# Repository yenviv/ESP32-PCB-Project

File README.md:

# ESP32-PCB-Project

https://docs.google.com/document/d/1k7oXqKPPIyiNBScuKdaxDys5A82Lqltt7Ke-TY6Z6dU/edit?usp=sharing

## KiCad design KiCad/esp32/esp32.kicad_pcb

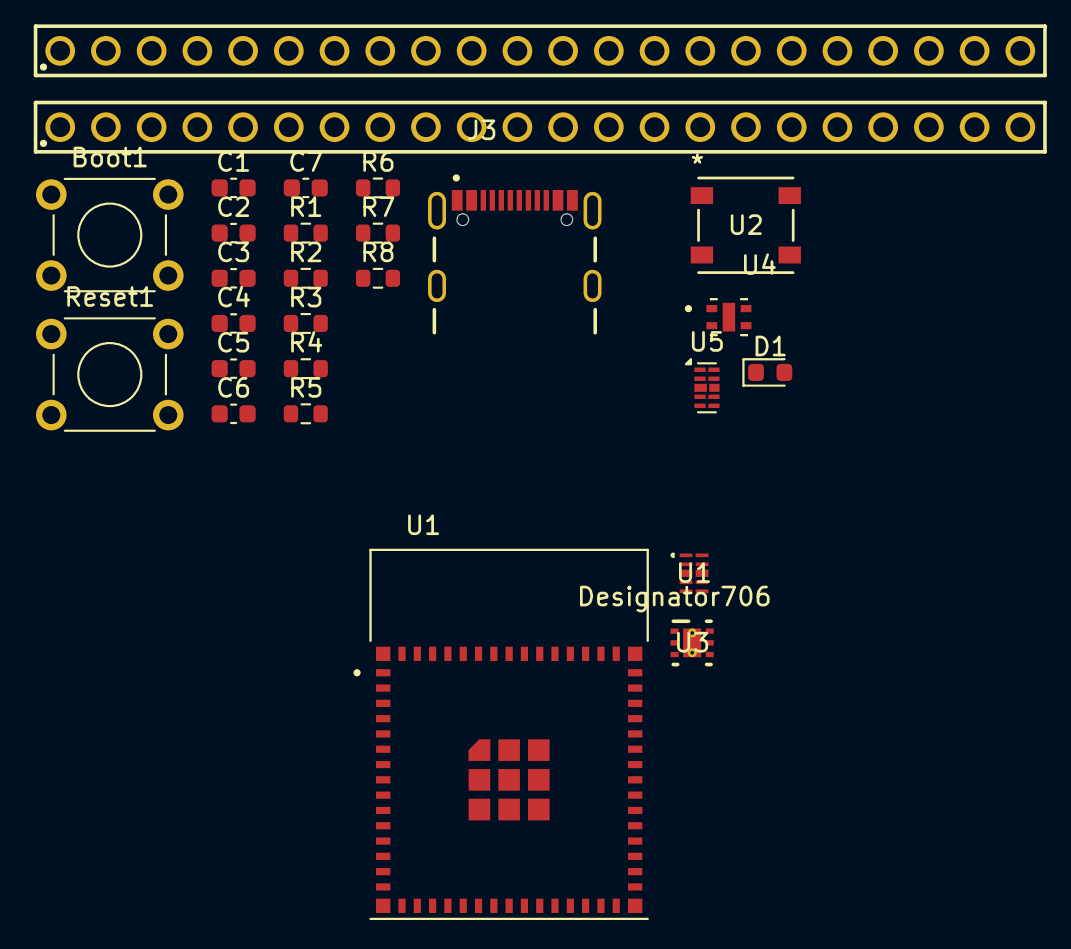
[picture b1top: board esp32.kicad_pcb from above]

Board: 2 copper layers, 27 parts (0 on the bottom side), 47 nets, no tracks yet.

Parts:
Boot1: SW_Push_Dual; SW_TH_Tactile_Omron_B3F-100x
C1, C2, C3, C7: 0.1u; C_0603_1608Metric
C4, C5, C6: 10u; C_0603_1608Metric
D1: LED; LED_0603_1608Metric
J1, J2: 6130XX11121_61302211121; 61302211121
J3: USB4105-GF-A; GCT_USB4105-GF-A
R1, R2, R3: 10k; R_0603_1608Metric
R4, R5, R8: 5.1k; R_0603_1608Metric
R6: 1M; R_0603_1608Metric
R7: 200k; R_0603_1608Metric
Reset1: SW_Push_Dual; SW_TH_Tactile_Omron_B3F-100x
U1: ESD7104MUTAG; UDFN10_ONS
U1#2: ESP32-S3-MINI-1-N8; XCVR_ESP32-S3-MINI-1-N8
U2: COM-16347; COM-16347_SPK
U3: TLV75801PDRVR; DRV0006A
U4: ENS210-LQFM; XDCR_ENS210-LQFM
U5: D3V3XA4B10LP; Diodes_UDFN-10_1.0x2.5mm_P0.5mm

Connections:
+3V3: C3.1, C4.1, C6.1, C7.1, J1.1, R1.2, R2.1, R3.1, R6.1, R8.2, U1#2.3 (3V3), U2.1 (VDD), U3.1 (OUT), U4.1 (VDD)
+5V: C5.1, J1.21, J3.A4_B9 (VBUS), J3.B4_A9 (VBUS__1), U3.4 (EN), U3.6 (IN), U5.4
/ESP32_EN: C1.1, J2.2, R2.2, Reset1.2, U1#2.45 (EN)
/GPI00: Boot1.2, C2.1, J1.2, U1#2.4 (IO0)
/GPI01: J1.3, U1#2.5 (IO1)
/GPI02: J1.4, U1#2.6 (IO2)
/GPI03: J1.5, U1#2.7 (IO3)
/GPI04: J1.6, U1#2.8 (IO4)
/GPI05: J1.7, U1#2.9 (IO5)
/GPI06: J1.8, U1#2.10 (IO6)
/GPI07: J1.9, U1#2.11 (IO7)
/GPI08: J1.10, U1#2.12 (IO8)
/GPI09: J1.11, U1#2.13 (IO9)
/GPI010: J1.12, U1#2.14 (IO10)
/GPI011: J1.13, U1#2.15 (IO11)
/GPI012: J1.14, U1#2.16 (IO12)
/GPI013: J1.15, U1#2.17 (IO13)
/GPI014: J1.16, U1#2.18 (IO14)
/GPI015: J1.17, U1#2.19 (IO15)
/GPI016: J1.18, U1#2.20 (IO16)
/GPI021: J2.18, U1#2.25 (IO21)
/GPI026: J2.17, U1#2.26 (IO26)
/GPI033: J2.16, U1#2.28 (IO33)
/GPI034: J2.15, U1#2.29 (IO34)
/GPI035: J2.14, U1#2.31 (IO35)
/GPI036: J2.13, U1#2.32 (IO36)
/GPI037: J2.12, U1#2.33 (IO37)
/GPI038: J2.11, U1#2.34 (IO38)
/GPI039: J2.10, U1#2.35 (IO39)
/GPI040: J2.9, U1#2.36 (IO40)
/GPI041: J2.8, U1#2.37 (IO41)
/GPI042: J2.7, U1#2.38 (IO42)
/GPI045: J2.4, U1#2.41 (IO45)
/GPI046: J2.3, U1#2.44 (IO46)
/GPI047: J2.22, U1#2.27 (IO47)
/GPI048: J2.21, U1#2.30 (IO48), U2.4 (DIN)
/I2C_SCL: J1.19, R3.2, U1#2.21 (IO17), U4.2 (SCL)
/I2C_SDA: J1.20, R1.1, U1#2.22 (IO18), U4.3 (SDA)
/RXD: J2.5, U1#2.40 (RXD0)
/TXD: J2.6, U1#2.39 (TXD0)
/USB_N: J2.19, J3.A7 (DN1), J3.B7 (DN2), U1#2.23 (IO19), U5.2
/USB_P: J2.20, J3.A6 (DP1), J3.B6 (DP2), U1#2.24 (IO20), U5.1
GND: Boot1.1, C1.2, C2.2, C3.2, C4.2, C5.2, C6.2, C7.2, D1.1 (K), J1.22, J2.1, J3.A1_B12 (GND), J3.B1_A12 (GND__1), J3.SH1 (SHELL_GND), J3.SH2 (SHELL_GND__1), J3.SH3 (SHELL_GND__2), J3.SH4 (SHELL_GND__3), R4.2, R5.2, R7.2, Reset1.1, U1#2.1 (GND), U1#2.2 (GND__1), U1#2.42 (GND__2), U1#2.43 (GND__3), U1#2.46 (GND__4), U1#2.47 (GND__5), U1#2.48 (GND__6), U1#2.49 (GND__7), U1#2.50 (GND__8), U1#2.51 (GND__9), U1#2.52 (GND__10), U1#2.53 (GND__11), U1#2.54 (GND__12), U1#2.55 (GND__13), U1#2.56 (GND__14), U1#2.57 (GND__15), U1#2.58 (GND__16), U1#2.59 (GND__17), U1#2.60 (GND__18), U1#2.61 (GND__19), U1#2.61_1 (GND__20), U1#2.61_2 (GND__21), U1#2.61_3 (GND__22), U1#2.61_4 (GND__23), U1#2.61_5 (GND__24), U1#2.61_6 (GND__25), U1#2.61_7 (GND__26), U1#2.61_8 (GND__27), U1#2.62 (GND__28), U1#2.63 (GND__29), U1#2.64 (GND__30), U1#2.65 (GND__31), U2.3 (VSS), U3.3 (GND), U3.7 (PAD), U4.4 (VSS), U4.5 (VSS__1), U5.3 (VSS), U5.8 (VSS)
unnamed: D1.2 (A), R8.1
unnamed: J3.A5 (CC1), R5.1
unnamed: J3.B5 (CC2), R4.1
unnamed: R6.2, R7.1, U3.2 (FB)

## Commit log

2025-11-27 Create KiCad
2025-12-02 update
    put esp32 sch into folder
2025-12-02 restructed the path and file strcter
    upaded schiemate and update pcb layout
2025-12-02 Added all symbols
    dowloaded and added all symbols expect for boot/restart
2025-12-04 worked on schematic
    Completed U4, led1, u3 usbj1, u5, j1, j3
2025-12-12 added reset and boot
2025-12-12 schemated complete erc pass
2025-12-12 layout started, footprints imported
    pushed pcb
